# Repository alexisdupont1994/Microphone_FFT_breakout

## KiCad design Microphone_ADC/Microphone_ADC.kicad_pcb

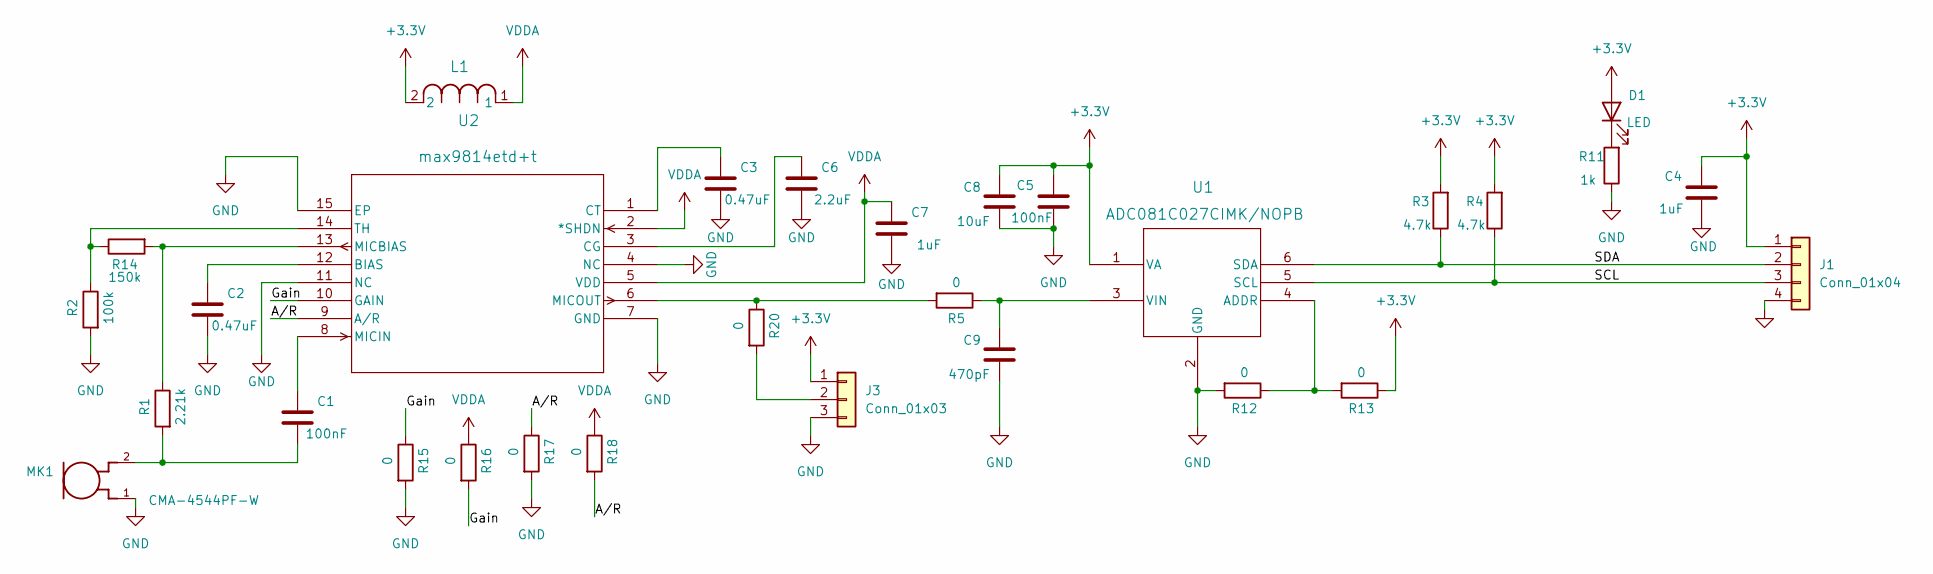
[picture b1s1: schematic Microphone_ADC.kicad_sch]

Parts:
C1, C5: 100nF; C_0805_2012Metric_Pad1.18x1.45mm_HandSolder
C2, C3: 0.47uF; C_0805_2012Metric_Pad1.18x1.45mm_HandSolder
C4: 1uF; C_1206_3216Metric_Pad1.33x1.80mm_HandSolder
C6: 2.2uF; C_0805_2012Metric_Pad1.18x1.45mm_HandSolder
C7: 1uF; C_0805_2012Metric_Pad1.18x1.45mm_HandSolder
C8: 10uF; C_1206_3216Metric_Pad1.33x1.80mm_HandSolder
C9: 470pF; C_0805_2012Metric_Pad1.18x1.45mm_HandSolder
D1: LED; LED_0805_2012Metric
J1: Conn_01x04; PinHeader_1x04_P2.54mm_Vertical
J3: Conn_01x03; PinHeader_1x03_P2.54mm_Vertical
L1: Ferrite_MMZ2012S601AT000; MMZ2012S601AT000-M
MK1: CMA-4544PF-W; MIC_CMA-4544PF-W
R1: 2.21k; R_0805_2012Metric_Pad1.20x1.40mm_HandSolder
R2: 100k; R_0805_2012Metric_Pad1.20x1.40mm_HandSolder
R3, R4: 4.7k; R_0805_2012Metric_Pad1.20x1.40mm_HandSolder
R5, R12, R13, R15, R16, R17, R18, R20: 0; R_0805_2012Metric_Pad1.20x1.40mm_HandSolder
R11: 1k; R_0805_2012Metric_Pad1.20x1.40mm_HandSolder
R14: 150k; R_0805_2012Metric_Pad1.20x1.40mm_HandSolder
U1: ADC081C027CIMK/NOPB; ADC081C027CIMK_NOPB-M
U2: max9814etd+t; max9814etd+t-M

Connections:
+3.3V: C4.1, C5.1, C8.2, D1.2 (A), J1.1, J3.1, L1.2, R3.2, R4.2, R13.1, U1.1 (VA)
/A/R: R17.1, R18.2, U2.9 (A/R)
/Gain: R15.1, R16.2, U2.10 (GAIN)
/SCL: J1.3, R4.1, U1.5 (SCL)
/SDA: J1.2, R3.1, U1.6 (SDA)
GND: C2.2, C3.2, C4.2, C5.2, C6.2, C7.2, C8.1, C9.1, J1.4, J3.3, MK1.1, R2.2, R11.1, R12.2, R15.2, R17.2, U1.2 (GND), U2.4 (NC), U2.7 (GND), U2.11 (NC), U2.15 (EP)
unnamed: C1.2, MK1.2, R1.2
unnamed: D1.1 (K), R11.2
unnamed: J3.2, R20.2
unnamed: R12.1, R13.2, U1.4 (ADDR)
unnamed: C9.2, R5.1, U1.3 (VIN)
unnamed: C2.1, U2.12 (BIAS)
unnamed: C6.1, U2.3 (CG)
unnamed: C3.1, U2.1 (CT)
unnamed: R1.1, R14.2, U2.13 (MICBIAS)
unnamed: C1.1, U2.8 (MICIN)
unnamed: R5.2, R20.1, U2.6 (MICOUT)
unnamed: R2.1, R14.1, U2.14 (TH)
VDDA: C7.1, L1.1, R16.1, R18.1, U2.2 (*SHDN), U2.5 (VDD)

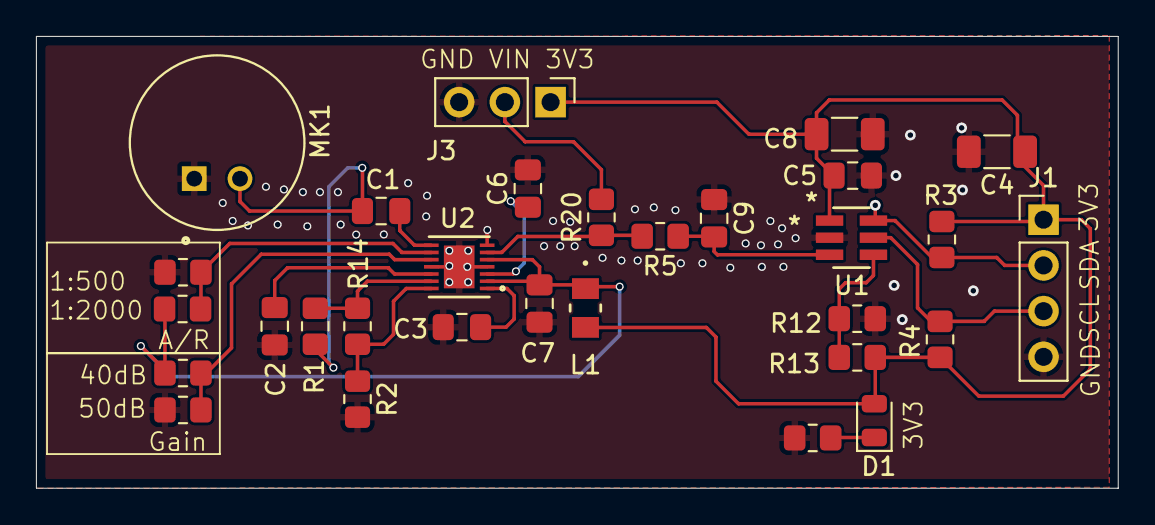
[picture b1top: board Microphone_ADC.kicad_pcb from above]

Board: 4 copper layers, 60.1 x 25.1 mm, 30 parts (0 on the bottom side), 19 nets.

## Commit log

2024-08-04 2024-08-03 : The MEMS didn't work, the soldering needed a stencil. Changing the microphone and the opamp for something specialized in it. Waiting for the board and to order new components
